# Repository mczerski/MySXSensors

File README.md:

View this project on [CADLAB.io](https://cadlab.io/project/1672). 

# MySXSensors

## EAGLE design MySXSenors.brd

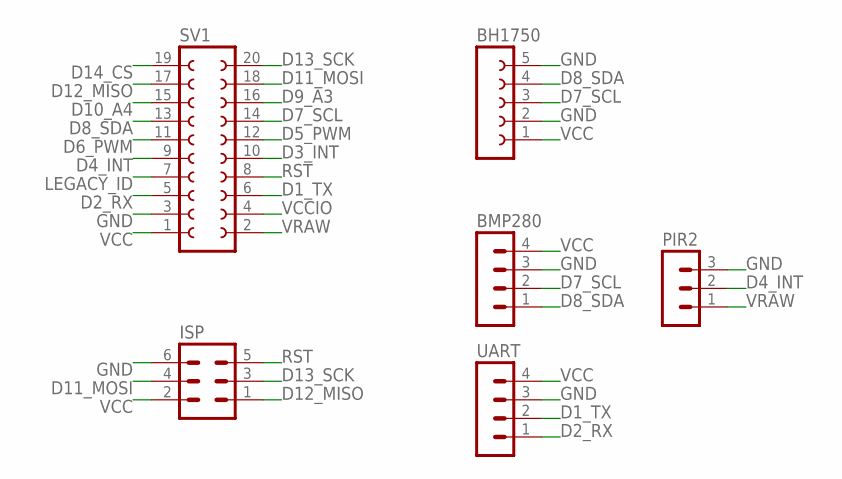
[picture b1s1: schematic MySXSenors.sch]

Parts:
BH1750: FE05-1
BMP280: MA04-1
ISP: MA03-2
PIR2: MA03-1
SV1: FE10-2
UART: MA04-1

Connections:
D1_TX: SV1.6, UART.2
D2_RX: SV1.5, UART.1
D3_INT: SV1.10
D4_INT: PIR2.2, SV1.9
D5_PWM: SV1.12
D6_PWM: SV1.11
D7_SCL: BH1750.3, BMP280.2, SV1.14
D8_SDA: BH1750.4, BMP280.1, SV1.13
D9_A3: SV1.16
D10_A4: SV1.15
D11_MOSI: ISP.4, SV1.18
D12_MISO: ISP.1, SV1.17
D13_SCK: ISP.3, SV1.20
D14_CS: SV1.19
GND: BH1750.2, BH1750.5, BMP280.3, ISP.6, PIR2.3, SV1.3, UART.3
LEGACY_ID: SV1.7
RST: ISP.5, SV1.8
VCC: BH1750.1, BMP280.4, ISP.2, SV1.1, UART.4
VCCIO: SV1.4
VRAW: PIR2.1, SV1.2

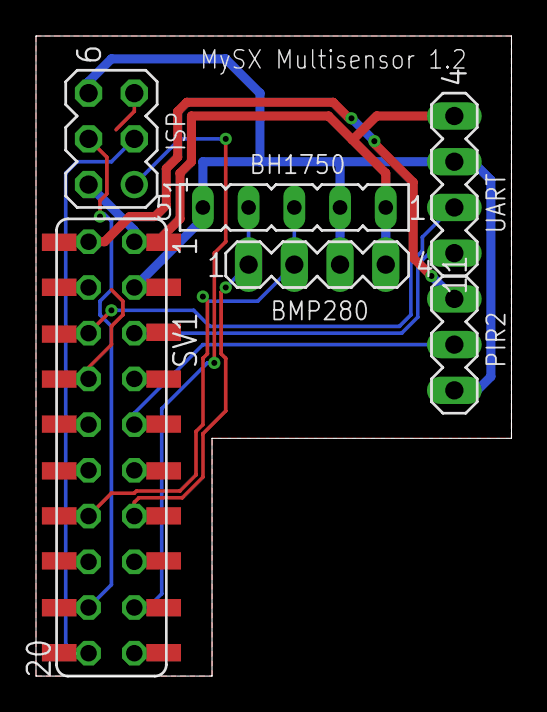
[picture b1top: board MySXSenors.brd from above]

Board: 2 copper layers, 26.4 x 35.6 mm, 6 parts (0 on the bottom side), 12 nets.

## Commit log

2018-02-01 add uart
2018-06-10 make MysX connector smd mounted
2019-04-03 Backlink to CADLAB.io has been added.
2019-04-03 rename DTM and DTF signals
2024-09-28 fix project name
2024-09-28 version 1.0
2025-01-03 move 2x10 pin socket to bottom side (and other components) + change positions of sensors
2025-01-14 change BME280 addr pin to gnd + move vias outside of pads
2025-04-27 add gas sensor
2025-04-27 add external connector for I2C
2025-05-18 add JST connector + pin headers for stability
2025-07-05 change motion signal assignment to D4_INT
2025-07-05 add lens footprint
